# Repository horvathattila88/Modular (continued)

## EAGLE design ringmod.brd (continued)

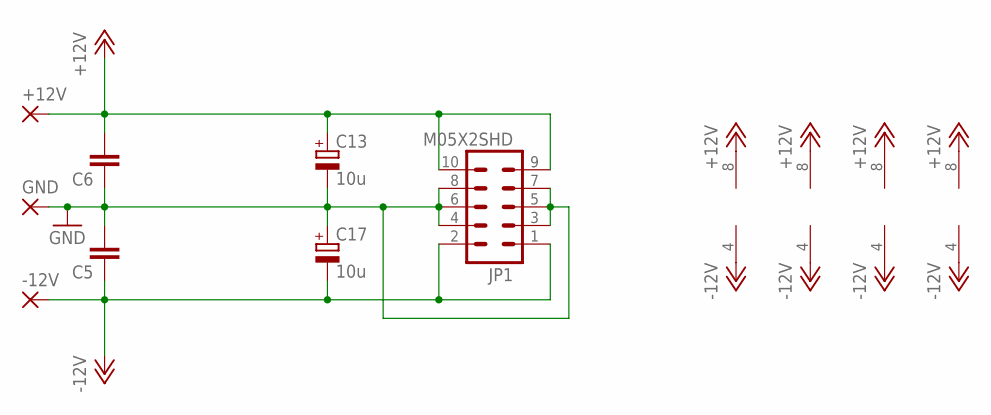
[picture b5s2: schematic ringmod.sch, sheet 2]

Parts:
+12V: 2,54/1,0
-12V: 2,54/1,0
C5, C6: C-EU050-035X075; C050-035X075
C13, C17: 10u; E3,5-8
GND: 2,54/1,0
IC1, IC2, IC4, IC5: TL082P; DIL08
JP1: M05X2SHD; 2X5-SHROUDED

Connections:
+12V: +12V.1, C6.2, C13.+, IC1.8 (V+), IC2.8 (V+), IC4.8 (V+), IC5.8 (V+), JP1.9, JP1.10; also elsewhere on the board
-12V: -12V.1, C5.1, C17.-, IC1.4 (V-), IC2.4 (V-), IC4.4 (V-), IC5.4 (V-), JP1.1, JP1.2; also elsewhere on the board
GND: C5.2, C6.1, C13.-, C17.+, GND.1, JP1.3, JP1.4, JP1.5, JP1.6, JP1.7, JP1.8; also elsewhere on the board

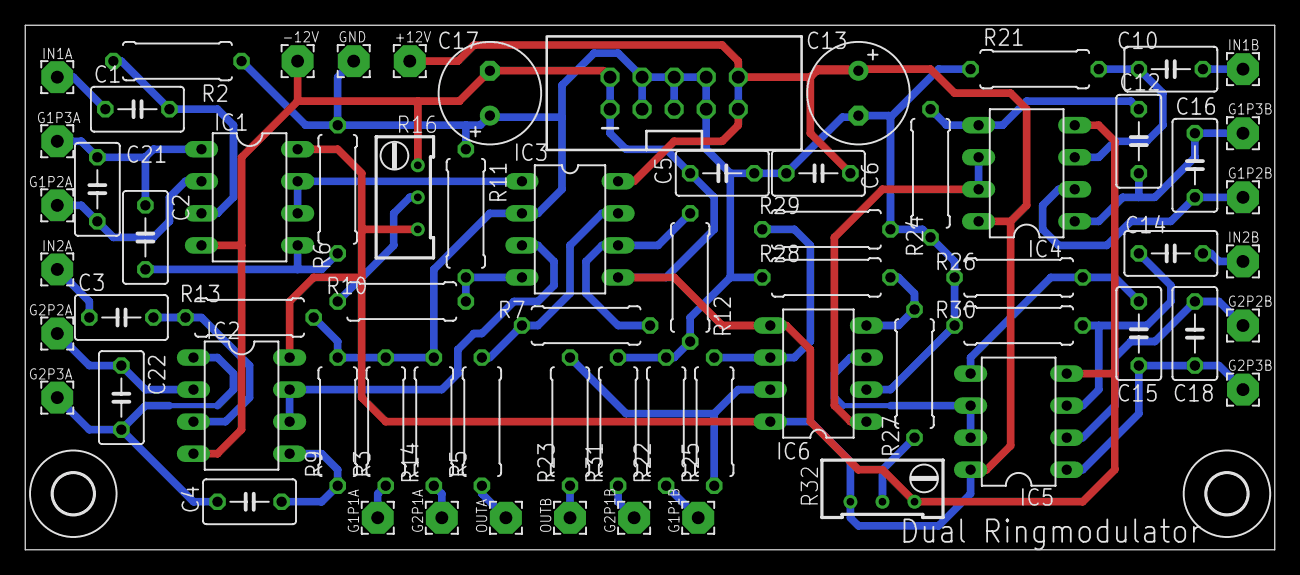
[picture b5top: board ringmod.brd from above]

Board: 2 copper layers, 99.0 x 41.6 mm, 70 parts (0 on the bottom side), 41 nets.

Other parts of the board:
U$1, U$2: 3,2

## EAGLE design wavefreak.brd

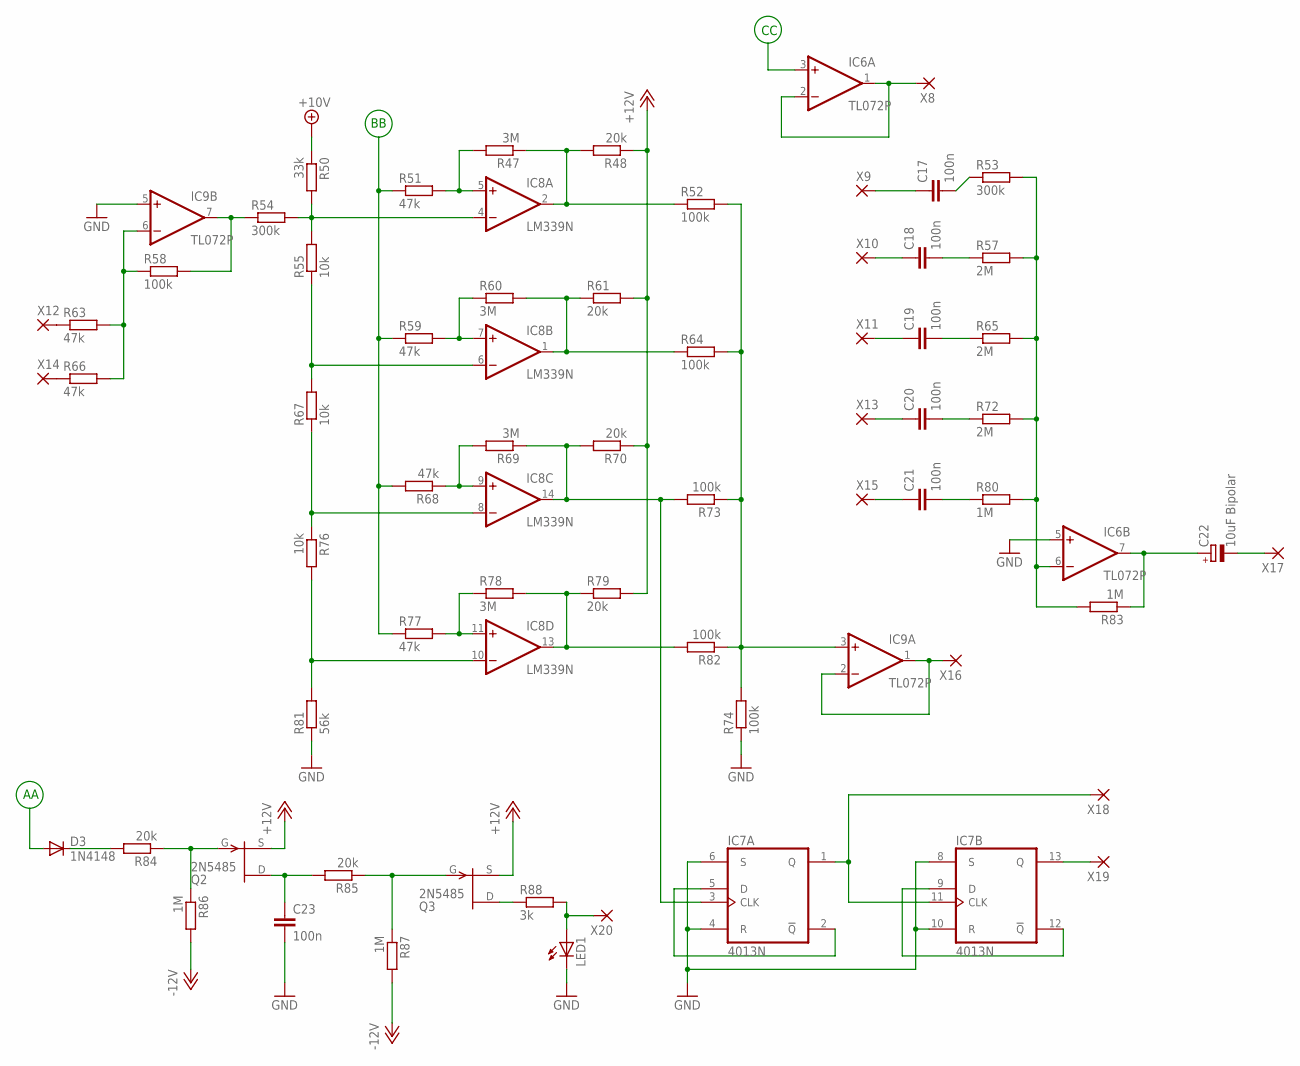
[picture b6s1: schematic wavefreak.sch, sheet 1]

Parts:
C17, C18, C19, C20, C21, C23: 100n; C050-025X075
C22: 10uF Bipolar; E3,5-8
D3: 1N4148; DO35-7
IC6, IC9: TL072P; DIL08
IC7: 4013N; DIL14
IC8: LM339N; DIL14
LED1: LED3MM
Q2, Q3: 2N5485; TO92-
R47, R60, R69, R78: 3M; 0309/10
R48, R61, R70, R79: 20k; 0309/10
R50: 33k; 0309/10
R51, R59, R68, R77: 47k; 0309/10
R52, R64, R73, R74, R82: 100k; 0309/10
R53, R54: 300k; 0309V
R55, R67, R76: 10k; 0309/10
R57, R65, R72: 2M; 0309V
R58: 100k; 0309V
R63, R66: 47k; 0309V
R80, R83, R86, R87: 1M; 0309V
R81: 56k; 0309/10
R84, R85: 20k; 0309V
R88: 3k; 0309V
X8, X9, X10, X11, X12, X13, X14, X15, X16, X17, X18, X19, X20: 2,54/1,0

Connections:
+10V: R50.1; also elsewhere on the board
+12V: Q2.2 (S), Q3.2 (S), R48.1, R61.2, R70.1, R79.2; also elsewhere on the board
-12V: R86.2, R87.2; also elsewhere on the board
AA: D3.A; also elsewhere on the board
BB: R51.1, R59.1, R68.2, R77.1; also elsewhere on the board
CC: IC6.3 (+IN); also elsewhere on the board
GND: C23.2, IC6.5 (+IN), IC7.4 (R), IC7.6 (S), IC7.8 (S), IC7.10 (R), IC9.5 (+IN), LED1.K (C), R74.1, R81.1; also elsewhere on the board
unnamed: C18.1, X10.1
unnamed: C17.2, R53.1
unnamed: C18.2, R57.1
unnamed: C19.2, R65.1
unnamed: C20.2, R72.1
unnamed: C21.2, R80.1
unnamed: C22.+, IC6.7 (OUT), R83.1
unnamed: LED1.A, R88.2, X20.1
unnamed: Q3.3 (D), R88.1
unnamed: IC6.6 (-IN), R53.2, R57.2, R65.2, R72.2, R80.2, R83.2
unnamed: C19.1, X11.1
unnamed: C20.1, X13.1
unnamed: C21.1, X15.1
unnamed: IC9.1 (OUT), IC9.2 (-IN), X16.1
unnamed: IC9.6 (-IN), R58.1, R63.2, R66.2
unnamed: R63.1, X12.1
unnamed: R66.1, X14.1
unnamed: IC9.7 (OUT), R54.1, R58.2
unnamed: IC8.4 (-IN), R50.2, R54.2, R55.2
unnamed: IC8.6 (-IN), R55.1, R67.2
unnamed: IC8.8 (-IN), R67.1, R76.1
unnamed: IC8.10 (-IN), R76.2, R81.2
unnamed: IC8.11 (+IN), R77.2, R78.1
unnamed: IC8.9 (+IN), R68.1, R69.2
unnamed: IC8.7 (+IN), R59.2, R60.1
unnamed: IC8.5 (+IN), R47.2, R51.2
unnamed: IC8.2 (OUT), R47.1, R48.2, R52.1
unnamed: IC8.1 (OUT), R60.2, R61.1, R64.1
unnamed: IC7.3 (CLK), IC8.14 (OUT), R69.1, R70.2, R73.2
unnamed: IC8.13 (OUT), R78.2, R79.1, R82.2
unnamed: IC9.3 (+IN), R52.2, R64.2, R73.1, R74.2, R82.1
unnamed: C17.1, X9.1
unnamed: Q3.1 (G), R85.1, R87.1
unnamed: C23.1, Q2.3 (D), R85.2
unnamed: IC7.2 (!Q), IC7.5 (D)
unnamed: IC7.1 (Q), IC7.11 (CLK), X18.1
unnamed: IC7.9 (D), IC7.12 (!Q)
unnamed: IC7.13 (Q), X19.1
unnamed: C22.-, X17.1
unnamed: Q2.1 (G), R84.1, R86.1
unnamed: D3.C, R84.2
unnamed: IC6.1 (OUT), IC6.2 (-IN), X8.1

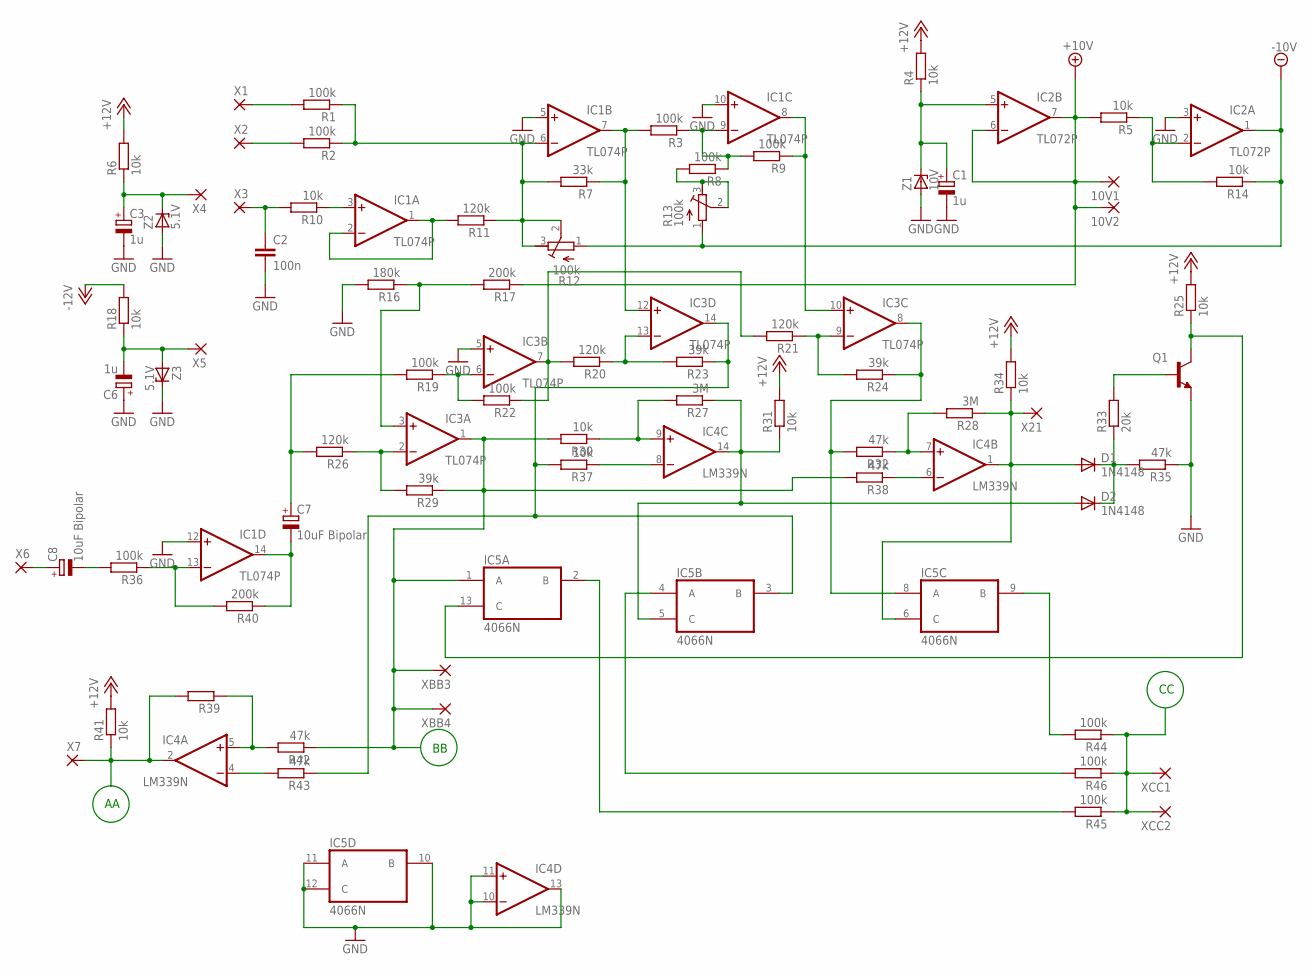
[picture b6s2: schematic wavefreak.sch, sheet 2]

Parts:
10V1, 10V2: 2,54/1,0
C1, C3, C6: 1u; E2,5-5
C2: 100n; C050-025X075
C7, C8: 10uF Bipolar; E3,5-8
D1, D2: 1N4148; DO35-7
IC1, IC3: TL074P; DIL14
IC2: TL072P; DIL08
IC4: LM339N; DIL14
IC5: 4066N; DIL14
Q1: 2N3904-NPN-TO92-EBC; TO92-EBC
R1, R2, R3, R8, R9, R19, R22, R36, R44, R45, R46: 100k; 0309V
R4, R5, R6, R10, R14, R18, R25, R30, R31, R34, R37, R41: 10k; 0309V
R7: 33k; 0309V
R11, R20, R21, R26: 120k; 0309V
R12, R13: 100k; RTRIM64W
R16: 180k; 0309V
R17, R40: 200k; 0309V
R23, R24, R29: 39k; 0309V
R27, R28: 3M; 0309V
R32, R35, R38, R42, R43: 47k; 0309V
R33: 20k; 0309V
R39: R-EU_0309/V; 0309V
X1, X2, X3, X4, X5, X6, X7, X21: 2,54/1,0
XBB3, XBB4: 2,54/1,0
XCC1, XCC2: 2,54/1,0
Z1: 10V; DO34Z7
Z2, Z3: 5.1V; DO34Z7

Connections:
+10V: 10V1.1, 10V2.1, IC2.6 (-IN), IC2.7 (OUT), R5.2, R17.1; also elsewhere on the board
+12V: R4.2, R6.2, R25.2, R31.2, R34.2, R41.2; also elsewhere on the board
-10V: IC2.1 (OUT), R12.1 (A), R13.1 (A), R14.1
-12V: R18.2; also elsewhere on the board
AA: IC4.2 (OUT), R39.2, R41.1, X7.1; also elsewhere on the board
BB: IC3.1 (OUT), IC5.1 (A), R29.1, R30.2, R38.2, R42.1, XBB3.1, XBB4.1; also elsewhere on the board
CC: R44.1, R45.1, R46.1, XCC1.1, XCC2.1; also elsewhere on the board
GND: C1.-, C2.2, C3.-, C6.+, IC1.5 (+IN), IC1.10 (+IN), IC1.12 (+IN), IC2.3 (+IN), IC3.5 (+IN), IC4.10 (-IN), IC4.11 (+IN), IC4.13 (OUT), IC5.10 (B), IC5.11 (A), IC5.12 (C), Q1.E, R16.2, R35.1, Z1.A, Z2.A, Z3.C; also elsewhere on the board
unnamed: R1.2, X1.1
unnamed: R2.2, X2.1
unnamed: IC1.6 (-IN), R1.1, R2.1, R7.2, R11.1, R12.2 (S), R12.3 (E)
unnamed: IC1.7 (OUT), IC3.12 (+IN), R3.2, R7.1
unnamed: IC1.9 (-IN), R3.1, R8.1, R9.2
unnamed: C2.1, R10.2, X3.1
unnamed: IC1.3 (+IN), R10.1
unnamed: IC1.1 (OUT), IC1.2 (-IN), R11.2
unnamed: C3.+, R6.1, X4.1, Z2.C
unnamed: C6.-, R18.1, X5.1, Z3.A
unnamed: C8.+, X6.1
unnamed: IC1.8 (OUT), IC3.10 (+IN), R9.1
unnamed: R8.2, R13.2 (S), R13.3 (E)
unnamed: C8.-, R36.2
unnamed: IC3.3 (+IN), R16.1, R17.2
unnamed: C7.-, IC1.14 (OUT), R40.1
unnamed: IC3.6 (-IN), R19.1, R22.2
unnamed: IC3.2 (-IN), R26.1, R29.2
unnamed: C7.+, R19.2, R26.2
unnamed: C1.+, IC2.5 (+IN), R4.1, Z1.C
unnamed: IC1.13 (-IN), R36.1, R40.2
unnamed: IC4.5 (+IN), R39.1, R42.2
unnamed: IC2.2 (-IN), R5.1, R14.2
unnamed: IC4.4 (-IN), R43.2
unnamed: IC4.9 (+IN), R27.2, R30.1
unnamed: IC4.8 (-IN), R37.1
unnamed: IC3.14 (OUT), IC5.3 (B), R23.1, R37.2, R43.1
unnamed: IC3.13 (-IN), R20.1, R23.2
unnamed: IC3.7 (OUT), R20.2, R21.2, R22.1
unnamed: IC3.9 (-IN), R21.1, R24.2
unnamed: D1.C, D2.C, R33.1, R35.2
unnamed: IC3.8 (OUT), IC5.8 (A), R24.1, R32.2
unnamed: D2.A, IC4.14 (OUT), IC5.5 (C), R27.1, R31.1
unnamed: Q1.B, R33.2
unnamed: IC4.6 (-IN), R38.1
unnamed: IC4.7 (+IN), R28.2, R32.1
unnamed: IC5.13 (C), Q1.C, R25.1
unnamed: D1.A, IC4.1 (OUT), IC5.6 (C), R28.1, R34.1, X21.1
unnamed: IC5.9 (B), R44.2
unnamed: IC5.4 (A), R46.2
unnamed: IC5.2 (B), R45.2

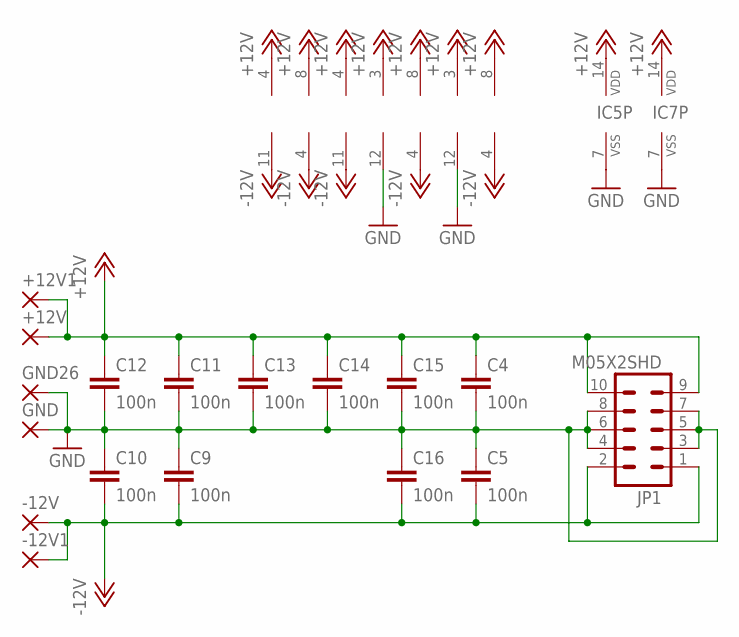
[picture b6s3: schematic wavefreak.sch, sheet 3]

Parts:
+12V, +12V1: 2,54/1,0
-12V, -12V1: 2,54/1,0
C4, C5, C9, C10, C11, C12, C13, C14, C15, C16: 100n; C025-025X050
GND, GND26: 2,54/1,0
IC1, IC3: TL074P; DIL14
IC2, IC6, IC9: TL072P; DIL08
IC4, IC8: LM339N; DIL14
IC5: 4066N; DIL14
IC7: 4013N; DIL14
JP1: M05X2SHD; 2X5-SHROUDED

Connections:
+12V: +12V.1, +12V1.1, C4.1, C11.1, C12.1, C13.1, C14.1, C15.1, IC1.4 (V+), IC2.8 (V+), IC3.4 (V+), IC4.3 (V+), IC5.14 (VDD), IC6.8 (V+), IC7.14 (VDD), IC8.3 (V+), IC9.8 (V+), JP1.9, JP1.10; also elsewhere on the board
-12V: -12V.1, -12V1.1, C5.2, C9.2, C10.2, C16.2, IC1.11 (V-), IC2.4 (V-), IC3.11 (V-), IC6.4 (V-), IC9.4 (V-), JP1.1, JP1.2; also elsewhere on the board
GND: C4.2, C5.1, C9.1, C10.1, C11.2, C12.2, C13.2, C14.2, C15.2, C16.1, GND.1, GND26.1, IC4.12 (GND), IC5.7 (VSS), IC7.7 (VSS), IC8.12 (GND), JP1.3, JP1.4, JP1.5, JP1.6, JP1.7, JP1.8; also elsewhere on the board

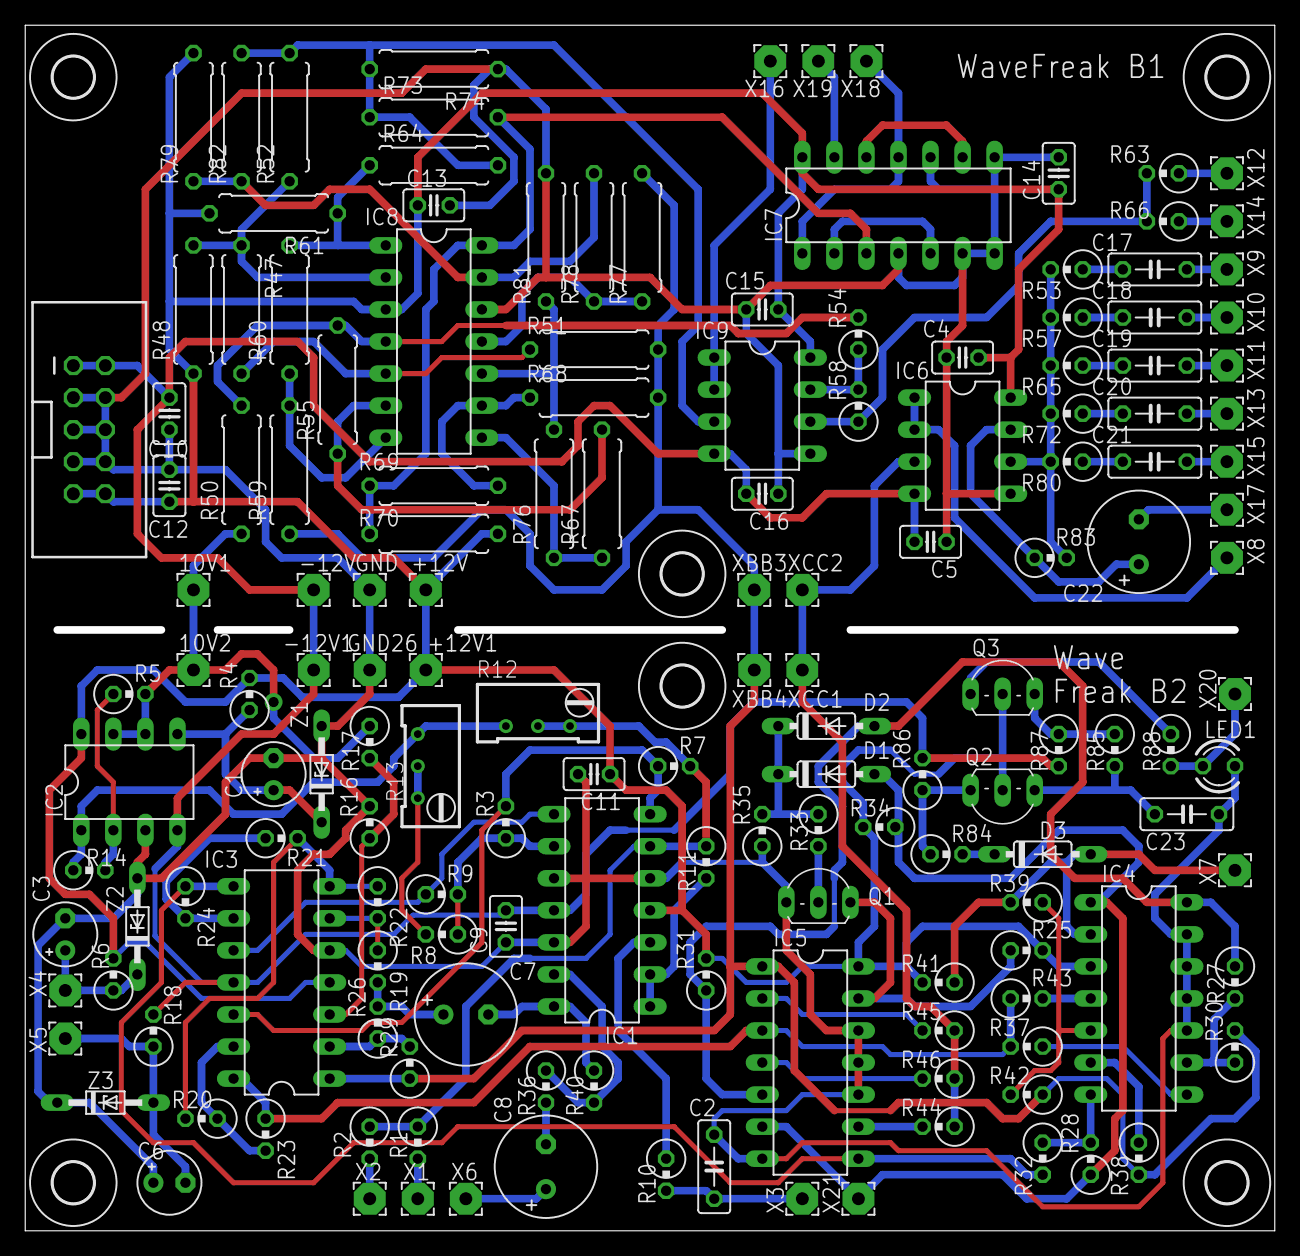
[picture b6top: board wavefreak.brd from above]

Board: 2 copper layers, 98.4 x 94.9 mm, 164 parts (0 on the bottom side), 91 nets.

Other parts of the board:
U$1, U$2, U$3, U$4, U$5, U$6: 3,2

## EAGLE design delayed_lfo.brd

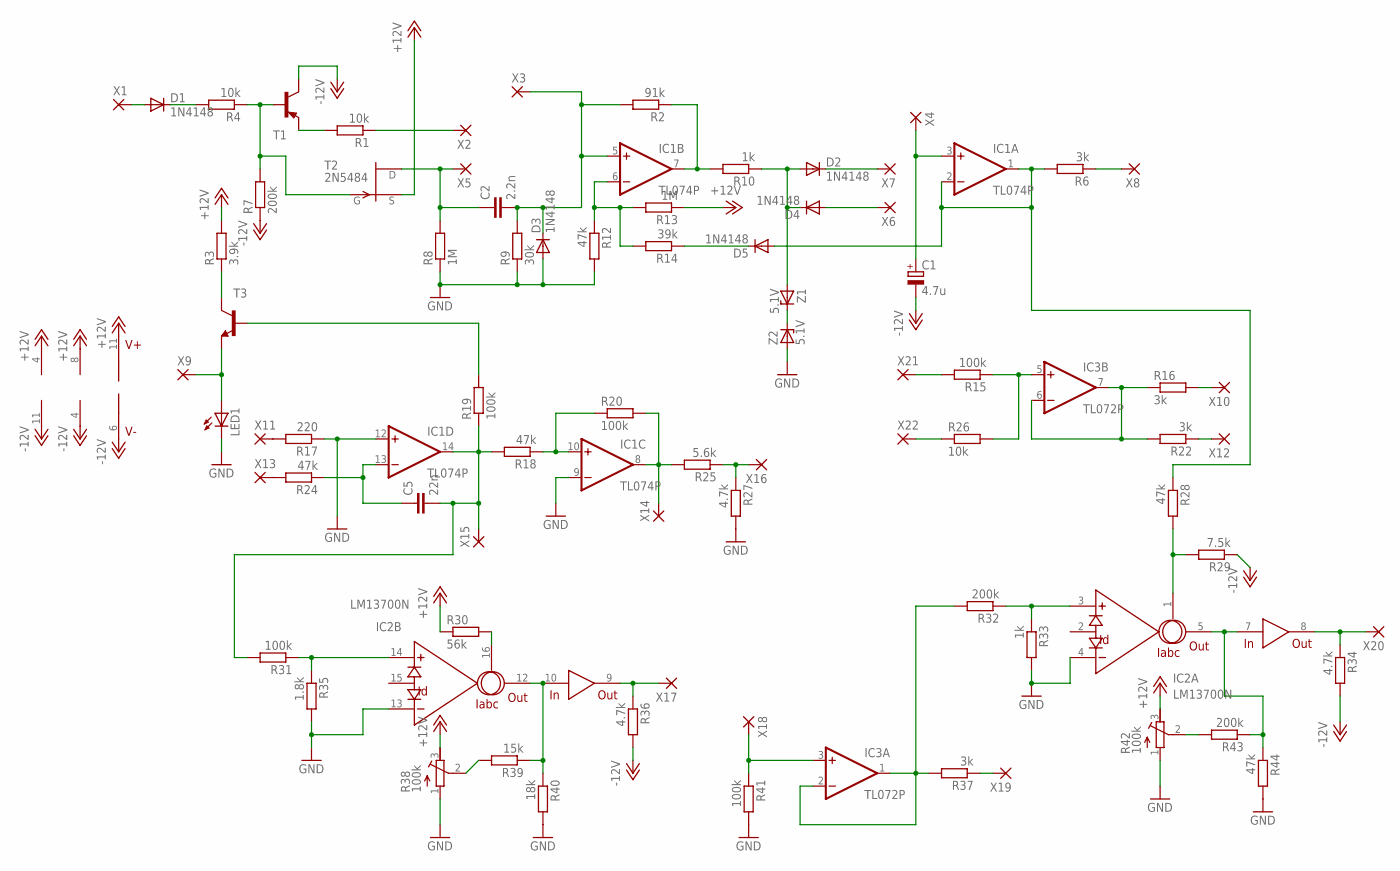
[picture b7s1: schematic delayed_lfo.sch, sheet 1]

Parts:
C1: 4.7u; E2-5
C2: 2.2n; C050-035X075
C5: 22n; C050-035X075
D1, D2, D3, D4, D5: 1N4148; DO35-7
IC1: TL074P; DIL14
IC2: LM13700N; DIL16
IC3: TL072P; DIL08
LED1: LED5MM
R1, R4, R26: 10k; 0309V
R2: 91k; 0309V
R3: 3.9k; 0309V
R6, R16, R22, R37: 3k; 0309V
R7, R43: 200k; 0309V
R8, R13: 1M; 0309V
R9: 30k; 0309V
R10, R33: 1k; 0309V
R12, R24, R28, R44: 47k; 0309V
R14: 39k; 0309V
R15, R19, R20, R31: 100k; 0309V
R17: 220; 0309V
R18: 47k; 0309/10
R25: 5.6k; 0309V
R27: 4.7k; 0309V
R29: 7.5k; 0309V
R30: 56k; 0309V
R32: 200k; 0309/10
R34, R36: 4.7k; 0309/10
R35: 1.8k; 0309V
R38, R42: 100k; RTRIM64W
R39: 15k; 0309/10
R40: 18k; 0309/10
R41: 100k; 0309/10
T1: 2N3906-PNP-TO92-EBC; TO92-EBC
T2: 2N5484; TO92-
T3: 2N3903-NPN-TO92-BEC; TO92-BEC
X1, X2, X3, X4, X5, X6, X7, X8, X9, X10, X11, X12, X13, X14, X15, X16, X17, X18, X19, X20, X21, X22: 2,54/1,0
Z1, Z2: 5.1V; DO34Z7

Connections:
+12V: IC1.4 (V+), IC2.11 (V+), IC3.8 (V+), R3.2, R13.1, R30.1, R38.3 (E), R42.3 (E), T2.2 (S); also elsewhere on the board
-12V: C1.-, IC1.11 (V-), IC2.6 (V-), IC3.4 (V-), R7.1, R29.1, R34.2, R36.2, T1.C; also elsewhere on the board
GND: D3.A, IC1.9 (-IN), IC1.12 (+IN), IC2.4 (-IN), IC2.13 (-IN), LED1.K (C), R8.1, R9.1, R12.2, R17.1, R27.2, R33.2, R35.2, R38.1 (A), R40.2, R41.2, R42.1 (A), R44.2, Z2.A; also elsewhere on the board
unnamed: D1.A, X1.1
unnamed: R1.1, X2.1
unnamed: R4.1, R7.2, T1.B, T2.1 (G)
unnamed: D1.C, R4.2
unnamed: R1.2, T1.E
unnamed: C2.1, R8.2, T2.3 (D), X5.1
unnamed: R3.1, T3.C
unnamed: LED1.A, T3.E, X9.1
unnamed: C5.2, IC1.14 (OUT), R18.2, R19.1, R31.2, X15.1
unnamed: R19.2, T3.B
unnamed: R17.2, X11.1
unnamed: R24.2, X13.1
unnamed: C5.1, IC1.13 (-IN), R24.1
unnamed: IC1.10 (+IN), R18.1, R20.1
unnamed: IC1.8 (OUT), R20.2, R25.2, X14.1
unnamed: R25.1, R27.1, X16.1
unnamed: IC3.3 (+IN), R41.1, X18.1
unnamed: IC2.9 (OUT), R36.1, X17.1
unnamed: IC2.14 (+IN), R31.1, R35.1
unnamed: IC2.10 (IN), IC2.12 (OUT), R39.1, R40.1
unnamed: IC2.16 (IABC), R30.2
unnamed: R38.2 (S), R39.2
unnamed: IC3.1 (OUT), IC3.2 (-IN), R32.2, R37.2
unnamed: R37.1, X19.1
unnamed: IC2.3 (+IN), R32.1, R33.1
unnamed: IC2.5 (OUT), IC2.7 (IN), R43.1, R44.1
unnamed: IC2.1 (IABC), R28.2, R29.2
unnamed: R42.2 (S), R43.2
unnamed: IC2.8 (OUT), R34.1, X20.1
unnamed: R15.2, X21.1
unnamed: IC3.5 (+IN), R15.1, R26.2
unnamed: R26.1, X22.1
unnamed: IC3.6 (-IN), IC3.7 (OUT), R16.1, R22.2
unnamed: R16.2, X10.1
unnamed: R22.1, X12.1
unnamed: IC1.7 (OUT), R2.1, R10.2
unnamed: C2.2, D3.C, IC1.5 (+IN), R2.2, R9.2, X3.1
unnamed: IC1.6 (-IN), R12.1, R13.2, R14.2
unnamed: D5.C, R14.1
unnamed: D5.A, IC1.1 (OUT), IC1.2 (-IN), R6.2, R28.1
unnamed: R6.1, X8.1
unnamed: Z1.C, Z2.C
unnamed: D2.A, D4.C, R10.1, Z1.A
unnamed: D4.A, X6.1
unnamed: D2.C, X7.1
unnamed: C1.+, IC1.3 (+IN), X4.1

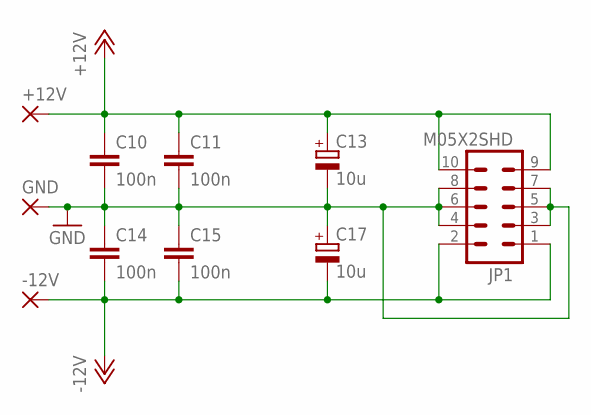
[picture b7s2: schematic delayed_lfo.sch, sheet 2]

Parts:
+12V: 2,54/1,0
-12V: 2,54/1,0
C10, C11, C14, C15: 100n; C050-035X075
C13, C17: 10u; E3,5-8
GND: 2,54/1,0
JP1: M05X2SHD; 2X5-SHROUDED

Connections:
+12V: +12V.1, C10.1, C11.1, C13.+, JP1.9, JP1.10; also elsewhere on the board
-12V: -12V.1, C14.2, C15.2, C17.-, JP1.1, JP1.2; also elsewhere on the board
GND: C10.2, C11.2, C13.-, C14.1, C15.1, C17.+, GND.1, JP1.3, JP1.4, JP1.5, JP1.6, JP1.7, JP1.8; also elsewhere on the board

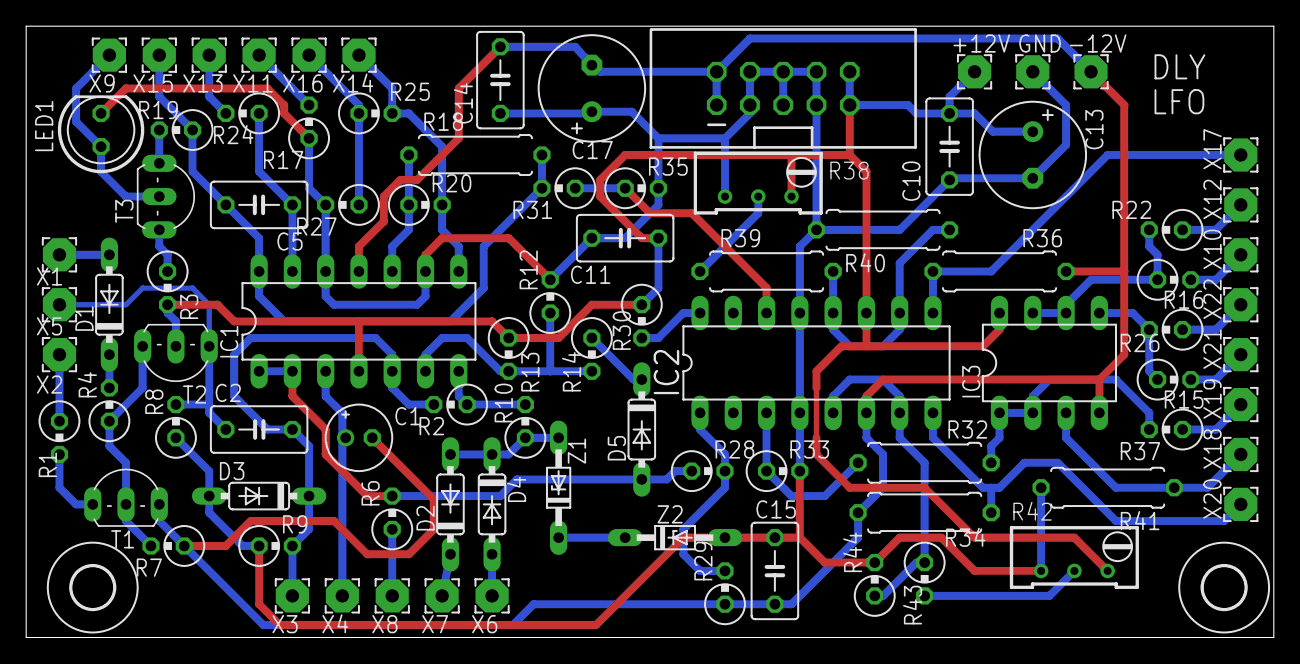
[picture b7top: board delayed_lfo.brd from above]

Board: 2 copper layers, 95.2 x 46.7 mm, 91 parts (0 on the bottom side), 49 nets.

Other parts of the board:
U$1, U$2: 3,2

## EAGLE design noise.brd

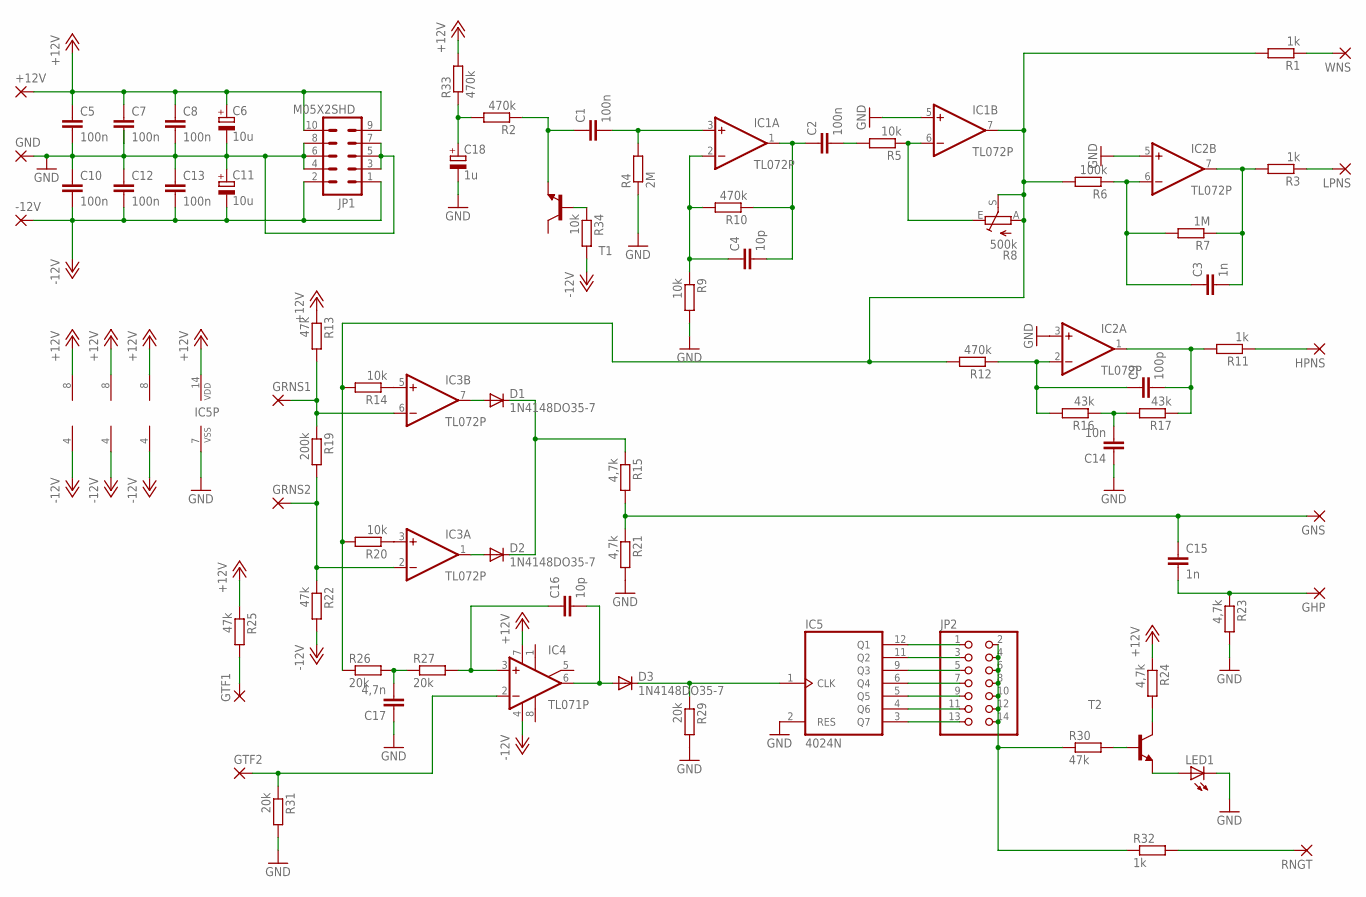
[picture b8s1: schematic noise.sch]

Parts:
+12V: 2,54/1,0
-12V: 2,54/1,0
C1, C2, C5, C7, C8, C10, C12, C13: 100n; C050-035X075
C3, C15: 1n; C050-035X075
C4, C16: 10p; C050-035X075
C6, C11: 10u; E2,5-6
C9: 100p; C050-035X075
C14: 10n; C050-035X075
C17: 4,7n; C050-035X075
C18: 1u; E2-5
D1, D2, D3: 1N4148DO35-7; DO35-7
GHP: 2,54/1,0
GND: 2,54/1,0
GNS: 2,54/1,0
GRNS1, GRNS2: 2,54/1,0
GTF1, GTF2: 2,54/1,0
HPNS: 2,54/1,0
IC1, IC2, IC3: TL072P; DIL08
IC4: TL071P; DIL08
IC5: 4024N; DIL14
JP1: M05X2SHD; 2X5-SHROUDED
JP2: PINHD-2X7; 2X07
LED1: LED3MM
LPNS: 2,54/1,0
R1, R3, R11, R32: 1k; 0309/10
R2, R10, R12, R33: 470k; 0309/10
R4: 2M; 0309/10
R5, R9, R14, R20, R34: 10k; 0309/10
R6: 100k; 0309/10
R7: 1M; 0309/10
R8: 500k; RJ9W
R13, R22, R25, R30: 47k; 0309/10
R15, R21, R23, R24: 4,7k; 0309/10
R16, R17: 43k; 0309/10
R19: 200k; 0309/10
R26, R27, R29, R31: 20k; 0309/10
RNGT: 2,54/1,0
T1, T2: 2N3904-NPN-TO92-EBC; TO92-EBC
WNS: 2,54/1,0

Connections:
+12V: +12V.1, C5.1, C6.+, C7.1, C8.1, IC1.8 (V+), IC2.8 (V+), IC3.8 (V+), IC4.7 (V+), IC5.14 (VDD), JP1.9, JP1.10, R13.1, R24.1, R25.1, R33.2
-12V: -12V.1, C10.2, C11.-, C12.2, C13.2, IC1.4 (V-), IC2.4 (V-), IC3.4 (V-), IC4.4 (V-), JP1.1, JP1.2, R22.2, R34.2
GND: C5.2, C6.-, C7.2, C8.2, C10.1, C11.+, C12.1, C13.1, C14.1, C17.1, C18.-, GND.1, IC1.5 (+IN), IC2.3 (+IN), IC2.5 (+IN), IC5.2 (RES), IC5.7 (VSS), JP1.3, JP1.4, JP1.5, JP1.6, JP1.7, JP1.8, LED1.K (C), R4.1, R9.2, R21.2, R23.2, R29.2, R31.2
unnamed: C18.+, R2.2, R33.1
unnamed: C1.1, R2.1, T1.E
unnamed: R34.1, T1.B
unnamed: C1.2, IC1.3 (+IN), R4.2
unnamed: C4.1, IC1.2 (-IN), R9.1, R10.2
unnamed: C15.2, GHP.1, R23.1
unnamed: C2.2, R5.2
unnamed: IC1.6 (-IN), R5.1, R8.E
unnamed: IC1.7 (OUT), R1.2, R6.2, R8.A, R8.S, R12.2, R14.2, R20.2, R26.1
unnamed: R1.1, WNS.1
unnamed: C3.1, IC2.6 (-IN), R6.1, R7.2
unnamed: C3.2, IC2.7 (OUT), R3.2, R7.1
unnamed: LPNS.1, R3.1
unnamed: C9.1, IC2.2 (-IN), R12.1, R16.2
unnamed: C14.2, R16.1, R17.2
unnamed: C9.2, IC2.1 (OUT), R11.2, R17.1
unnamed: HPNS.1, R11.1
unnamed: IC3.5 (+IN), R14.1
unnamed: IC3.3 (+IN), R20.1
unnamed: GRNS1.1, IC3.6 (-IN), R13.2, R19.1
unnamed: GRNS2.1, IC3.2 (-IN), R19.2, R22.1
unnamed: D1.A, IC3.7 (OUT)
unnamed: D2.A, IC3.1 (OUT)
unnamed: D1.C, D2.C, R15.1
unnamed: C15.1, GNS.1, R15.2, R21.1
unnamed: GTF2.1, IC4.2 (-IN), R31.1
unnamed: GTF1.1, R25.2
unnamed: C16.2, D3.A, IC4.6 (OUT)
unnamed: C16.1, IC4.3 (+IN), R27.2
unnamed: C17.2, R26.2, R27.1
unnamed: D3.C, IC5.1 (CLK), R29.1
unnamed: IC5.12 (Q1), JP2.1
unnamed: IC5.11 (Q2), JP2.3
unnamed: IC5.9 (Q3), JP2.5
unnamed: IC5.6 (Q4), JP2.7
unnamed: IC5.5 (Q5), JP2.9
unnamed: IC5.4 (Q6), JP2.11
unnamed: IC5.3 (Q7), JP2.13
unnamed: JP2.2, JP2.4, JP2.6, JP2.8, JP2.10, JP2.12, JP2.14, R30.1, R32.1
unnamed: R30.2, T2.B
unnamed: R24.2, T2.C
unnamed: LED1.A, T2.E
unnamed: R32.2, RNGT.1
unnamed: C2.1, C4.2, IC1.1 (OUT), R10.1

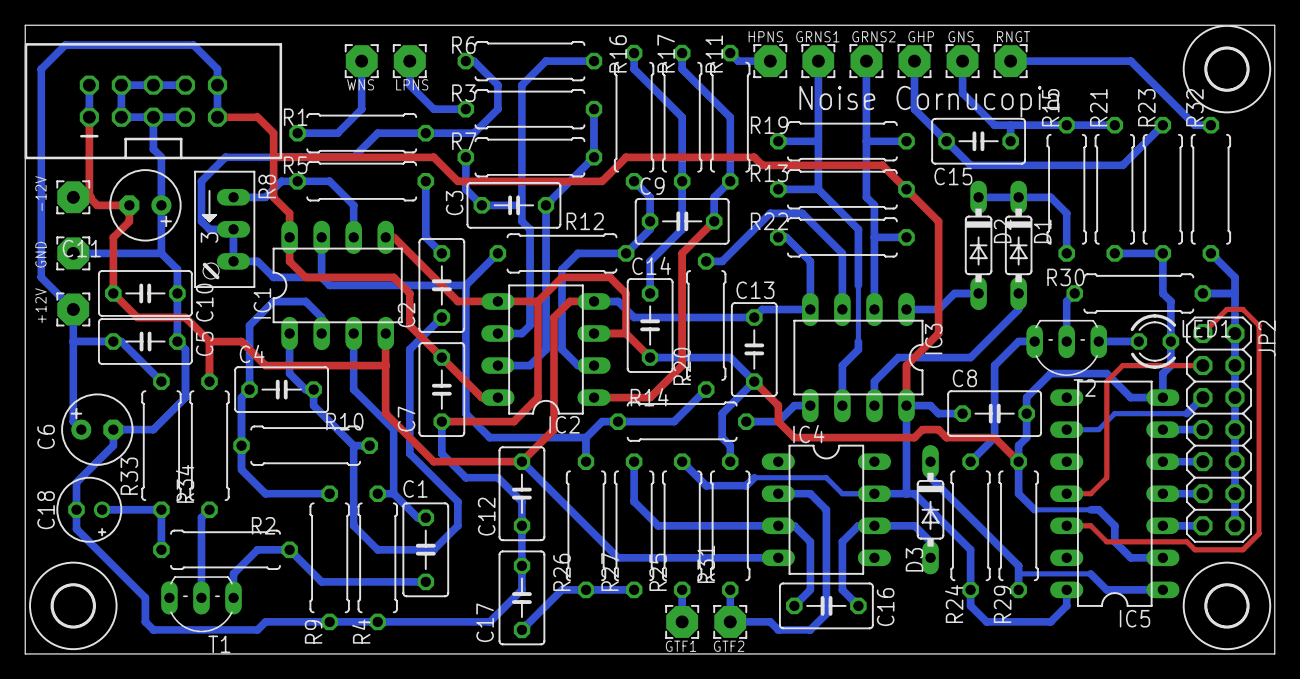
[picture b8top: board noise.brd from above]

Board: 2 copper layers, 99.0 x 49.8 mm, 79 parts (0 on the bottom side), 47 nets.

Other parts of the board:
U$1, U$2, U$3: 3,2
